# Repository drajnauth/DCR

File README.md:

# DCR
Direct Conversion Receiver

Various files for the DCR

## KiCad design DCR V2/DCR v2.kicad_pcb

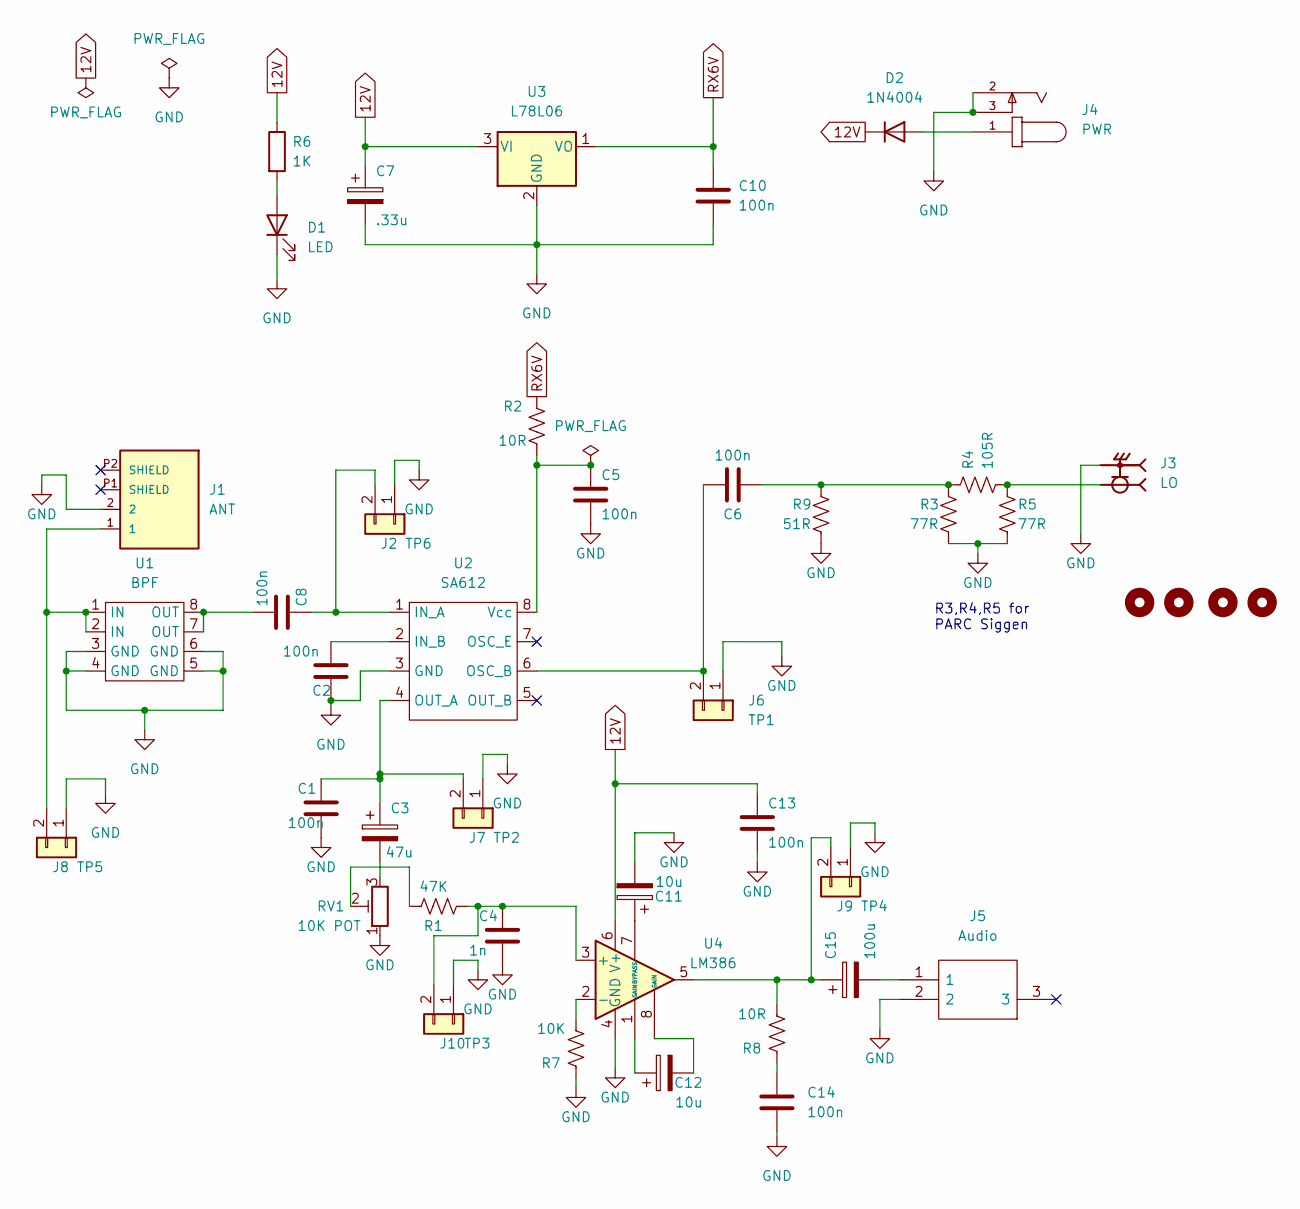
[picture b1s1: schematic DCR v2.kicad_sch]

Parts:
C1, C2, C5, C6, C8, C10, C13, C14: 100n; C_1206_3216Metric
C3: 47u; CP_Radial_D8.0mm_P2.50mm
C4: 1n; C_1206_3216Metric
C7: .33u; CP_Radial_D8.0mm_P2.50mm
C11, C12: 10u; CP_Radial_D8.0mm_P2.50mm
C15: 100u; CP_Radial_D8.0mm_P2.50mm
D1: LED; LED_D3.0mm
D2: 1N4004; D_DO-41_SOD81_P10.16mm_Horizontal
H1, H2, H3, H4: MountingHole; MountingHole_3.2mm_M3
J1: ANT; CONN_1-1337543-0
J2: TP6; PinHeader_1x02_P2.54mm_Vertical
J3: LO; RFSOLUTIONS_CON-SMA-EDGE-S; PARTREV 1
J4: PWR; CUI_PJ-002A
J5: Audio; 48322230; Manufacturer_Part_Number 4832.2230; Mouser Part Number 693-4832.223
J6: TP1; PinHeader_1x02_P2.54mm_Vertical
J7: TP2; PinHeader_1x02_P2.54mm_Vertical
J8: TP5; PinHeader_1x02_P2.54mm_Vertical
J9: TP4; PinHeader_1x02_P2.54mm_Vertical
J10: TP3; PinHeader_1x02_P2.54mm_Vertical
R1: 47K; R_1206_3216Metric
R2, R8: 10R; R_1206_3216Metric
R3, R5: 77R; R_Axial_DIN0207_L6.3mm_D2.5mm_P7.62mm_Horizontal
R4: 105R; R_Axial_DIN0207_L6.3mm_D2.5mm_P7.62mm_Horizontal
R6: 1K; R_1206_3216Metric
R7: 10K; R_1206_3216Metric
R9: 51R; R_Axial_DIN0207_L6.3mm_D2.5mm_P7.62mm_Horizontal
RV1: 10K POT; Bourns_PTV09A_Horizontal_Pot
U1: BPF; QRPLabs_Filter_TH
U2: SA612; DIP-8_W7.62mm_Socket
U3: L78L06; TO-92_Inline
U4: LM386; DIP-8_W7.62mm_Socket

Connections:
12V: C7.1, C13.1, D2.1 (K), R6.1, U3.3 (VI), U4.6 (V+)
GND: C1.2, C2.2, C4.2, C5.2, C7.2, C10.2, C11.2, C13.2, C14.2, D1.1 (K), J1.2, J2.1, J3.G1, J3.G2, J3.G3, J3.G4, J4.2, J4.3, J5.2, J6.1, J7.1, J8.1, J9.1, J10.1, R3.2, R5.2, R7.1, R9.2, RV1.1, U1.3 (GND), U1.4 (GND), U1.5 (GND), U1.6 (GND), U2.3 (GND), U3.2 (GND), U4.4 (GND)
unnamed: C1.1, C3.1, J7.2, U2.4 (OUT_A)
unnamed: C2.1, U2.2 (IN_B)
unnamed: C3.2, RV1.3
unnamed: C4.1, J10.2, R1.2, U4.3 (+)
unnamed: C5.1, R2.2, U2.8 (Vcc)
unnamed: C6.1, R3.1, R4.1, R9.1
unnamed: C6.2, J6.2, U2.6 (OSC_B)
unnamed: C8.1, U1.7 (OUT), U1.8 (OUT)
unnamed: C8.2, J2.2, U2.1 (IN_A)
unnamed: C11.1, U4.7 (BYPASS)
unnamed: C12.1, U4.1 (GAIN)
unnamed: C12.2, U4.8 (GAIN)
unnamed: C14.1, R8.1
unnamed: C15.1, J9.2, R8.2, U4.5
unnamed: C15.2, J5.1
unnamed: D1.2 (A), R6.2
unnamed: D2.2 (A), J4.1
unnamed: J1.1, J8.2, U1.1 (IN), U1.2 (IN)
unnamed: J3.1, R4.2, R5.1
unnamed: R1.1, RV1.2
unnamed: R7.2, U4.2 (-)
RX6V: C10.1, R2.1, U3.1 (VO)

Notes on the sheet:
R3,R4,R5 for PARC Siggen

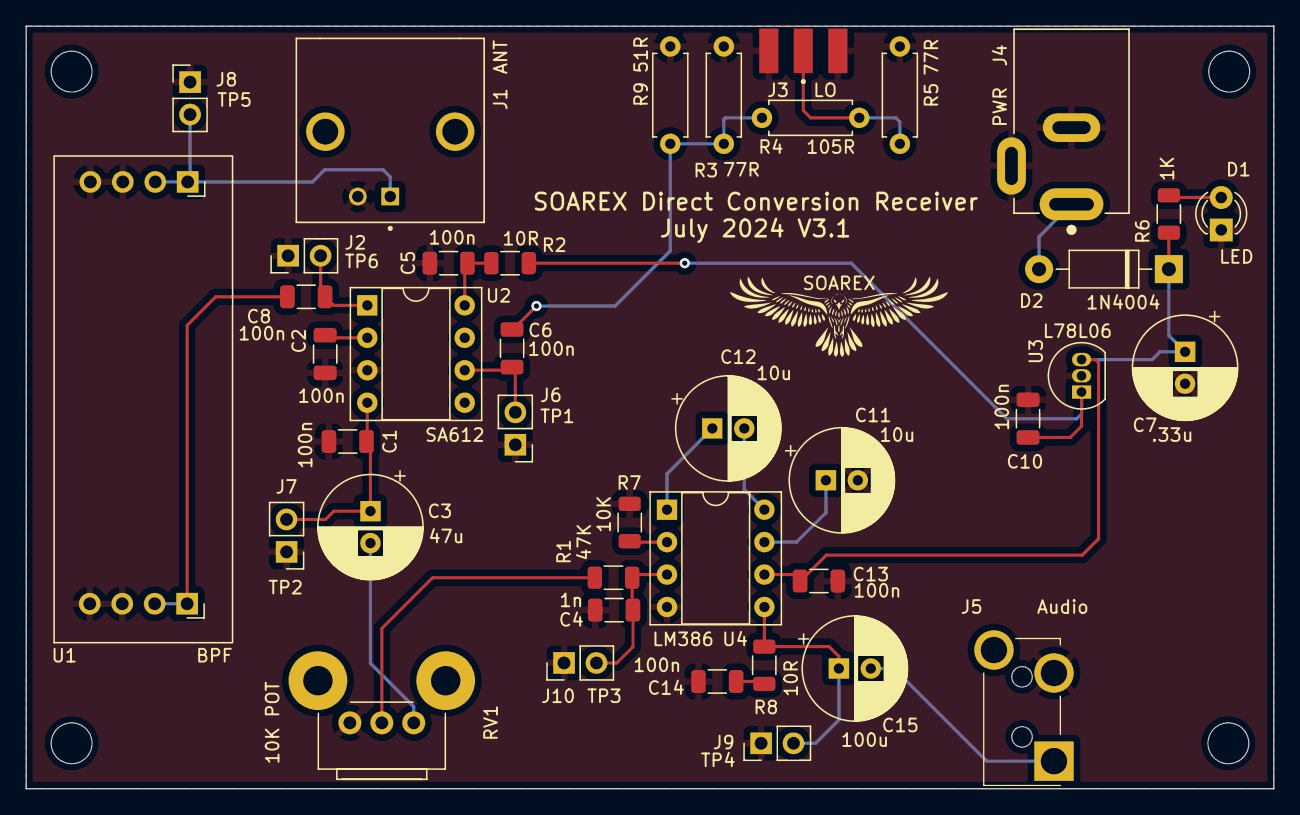
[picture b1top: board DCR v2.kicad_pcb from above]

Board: 2 copper layers, 97.7 x 59.7 mm, 44 parts (0 on the bottom side), 24 nets.

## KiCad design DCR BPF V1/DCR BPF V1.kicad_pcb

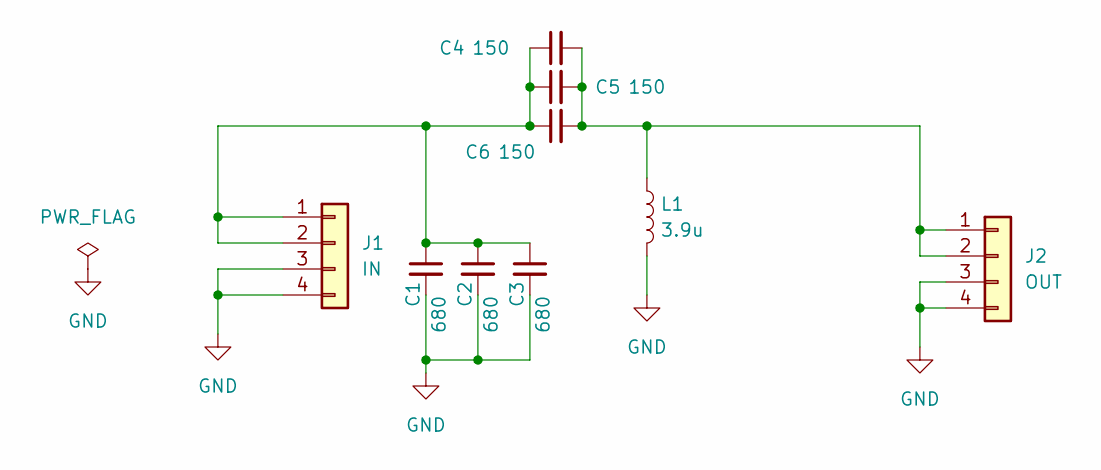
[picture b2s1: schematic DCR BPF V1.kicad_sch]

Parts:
C1, C2, C3: 680; C_Disc_D5.0mm_W2.5mm_P2.50mm
C4, C5, C6: 150; C_Disc_D5.0mm_W2.5mm_P2.50mm
J1: IN; PinHeader_1x04_P2.54mm_Vertical
J2: OUT; PinHeader_1x04_P2.54mm_Vertical
L1: 3.9u; L_Toroid_Vertical_L10.0mm_W5.0mm_P5.08mm

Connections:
GND: C1.2, C2.2, C3.2, J1.3, J1.4, J2.3, J2.4, L1.2
unnamed: C1.1, C2.1, C3.1, C4.1, C5.1, C6.1, J1.1, J1.2
unnamed: C4.2, C5.2, C6.2, J2.1, J2.2, L1.1

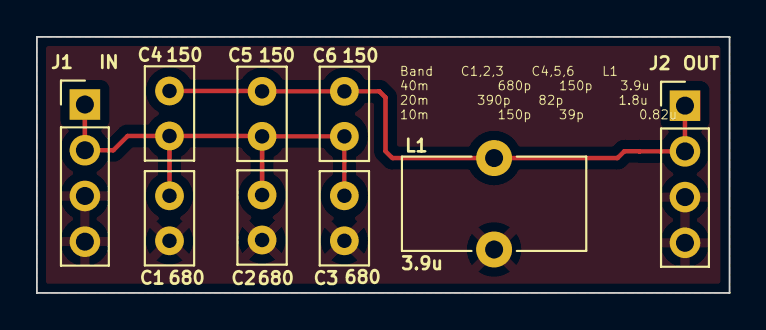
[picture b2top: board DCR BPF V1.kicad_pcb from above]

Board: 2 copper layers, 38.5 x 14.2 mm, 9 parts (0 on the bottom side), 3 nets.

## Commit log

2022-11-02 Nov 2 Update
2022-11-02 Add custom footprints
2022-11-03 Update snapada
2022-11-03 Updated exports
2022-11-04 VE3POA Update & Gerbers
2023-03-17 Added_Version_2
2023-03-19 Added SOAREX Logo
2024-07-20 Update Reg and Silk
2024-07-20 Cleanup
2024-07-20 Added backup file
2024-07-22 7896 Update
